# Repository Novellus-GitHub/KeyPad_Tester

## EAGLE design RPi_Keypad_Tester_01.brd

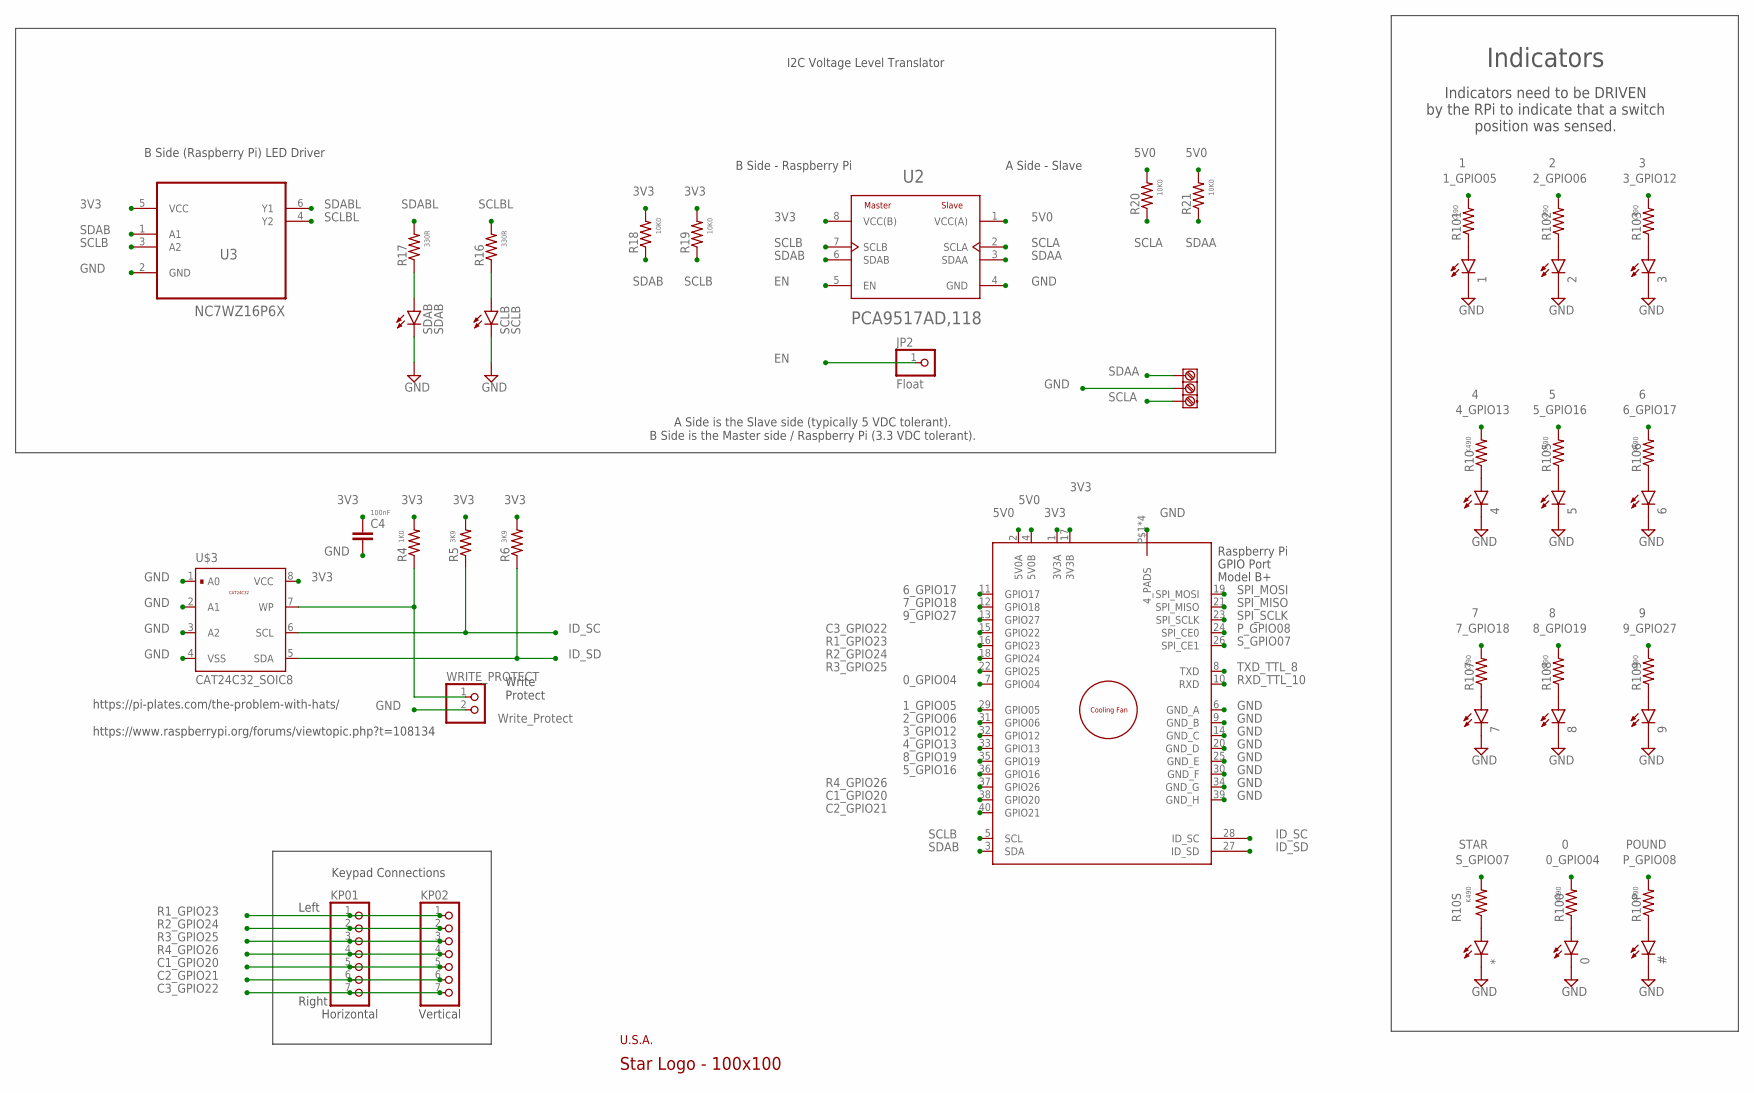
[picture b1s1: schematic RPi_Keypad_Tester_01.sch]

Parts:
0: 0; SML1206
1: 1; SML1206
2: 2; SML1206
3: 3; SML1206
4: 4; SML1206
5: 5; SML1206
6: 6; SML1206
7: 7; SML1206
8: 8; SML1206
9: 9; SML1206
#: POUND; SML1206
*: STAR; SML1206
C4: 100nF; C0805
JP2: Float; 1X01
KP01: PINHD-1X7/90; 1X07/90
KP02: PINHD-1X7; 1X07
R4: 1K0; RES_1206
R5, R6: 3K9; RES_1206
R10, R10P, R10S, R100, R101, R102, R103, R105, R106, R107, R108, R109: K490; RES_1206
R16, R17: 330R; RES_1206
R18, R19, R20, R21: 10K0; RES_1206
SCLB: SCLB; SML1206
SDAB: SDAB; SML1206
U2: PCA9517AD,118; SOIC127P600X175-8N
U3: NC7WZ16P6X; SOT65P210X110-6N
U$1: USA_01
U$2: 3_POSITION_3.81
U$3: CAT24C32_SOIC8
U$4: STAR_LOGO_01
WRITE_PROTECT: Write_Protect; 1X02
X1: RASPI_BOARD_B+#2_HDC; RASPI_BOARD_B+HAT_DF_CF

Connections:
0_GPIO04: R100.2, X1.7 (GPIO04)
1_GPIO05: R101.2, X1.29 (GPIO05)
2_GPIO06: R102.2, X1.31 (GPIO06)
3V3: C4.1, R4.2, R5.2, R6.2, R18.2, R19.2, U2.8 (VCC(B)), U3.5 (VCC), U$3.8 (VCC), X1.1 (3V3A), X1.17 (3V3B)
3_GPIO12: R103.2, X1.32 (GPIO12)
4_GPIO13: R10.2, X1.33 (GPIO13)
5V0: R20.2, R21.2, U2.1 (VCC(A)), X1.2 (5V0A), X1.4 (5V0B)
5_GPIO16: R105.2, X1.36 (GPIO16)
6_GPIO17: R106.2, X1.11 (GPIO17)
7_GPIO18: R107.2, X1.12 (GPIO18)
8_GPIO19: R108.2, X1.35 (GPIO19)
9_GPIO27: R109.2, X1.13 (GPIO27)
C1_GPIO20: KP01.5, KP02.5, X1.38 (GPIO20)
C2_GPIO21: KP01.6, KP02.6, X1.40 (GPIO21)
C3_GPIO22: KP01.7, KP02.7, X1.15 (GPIO22)
EN: JP2.1, U2.5 (EN)
GND: 0.C, 1.C, 2.C, 3.C, 4.C, 5.C, 6.C, 7.C, 8.C, 9.C, #.C, *.C, C4.2, SCLB.C, SDAB.C, U2.4 (GND), U3.2 (GND), U$2.2, U$3.1 (A0), U$3.2 (A1), U$3.3 (A2), U$3.4 (VSS), WRITE_PROTECT.2, X1.6 (GND_A), X1.9 (GND_B), X1.14 (GND_C), X1.20 (GND_D), X1.25 (GND_E), X1.30 (GND_F), X1.34 (GND_G), X1.39 (GND_H), X1.P$1 (4_PADS), X1.P$2 (4_PADS), X1.P$3 (4_PADS), X1.P$4 (4_PADS)
ID_SC: R5.1, U$3.6 (SCL), X1.28 (ID_SC)
ID_SD: R6.1, U$3.5 (SDA), X1.27 (ID_SD)
ID_WP1: R4.1, U$3.7 (WP), WRITE_PROTECT.1
unnamed: 1.A, R101.1
unnamed: 2.A, R102.1
unnamed: 3.A, R103.1
unnamed: 4.A, R10.1
unnamed: 5.A, R105.1
unnamed: 6.A, R106.1
unnamed: 7.A, R107.1
unnamed: 8.A, R108.1
unnamed: 9.A, R109.1
unnamed: *.A, R10S.1
unnamed: 0.A, R100.1
unnamed: #.A, R10P.1
unnamed: R16.1, SCLB.A
unnamed: R17.1, SDAB.A
P_GPIO08: R10P.2, X1.24 (SPI_CE0)
R1_GPIO23: KP01.1, KP02.1, X1.16 (GPIO23)
R2_GPIO24: KP01.2, KP02.2, X1.18 (GPIO24)
R3_GPIO25: KP01.3, KP02.3, X1.22 (GPIO25)
R4_GPIO26: KP01.4, KP02.4, X1.37 (GPIO26)
RXD_TTL_10: X1.10 (RXD)
SCLA: R20.1, U2.2 (SCLA), U$2.1
SCLB: R19.1, U2.7 (SCLB), U3.3 (A2), X1.5 (SCL)
SCLBL: R16.2, U3.4 (Y2)
SDAA: R21.1, U2.3 (SDAA), U$2.3
SDAB: R18.1, U2.6 (SDAB), U3.1 (A1), X1.3 (SDA)
SDABL: R17.2, U3.6 (Y1)
SPI_MISO: X1.21 (SPI_MISO)
SPI_MOSI: X1.19 (SPI_MOSI)
SPI_SCLK: X1.23 (SPI_SCLK)
S_GPIO07: R10S.2, X1.26 (SPI_CE1)
TXD_TTL_8: X1.8 (TXD)

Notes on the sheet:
Write Protect
https://pi-plates.com/the-problem-with-hats/ https://www.raspberrypi.org/forums/viewtopic.php?t=108134
Keypad Connections
Vertical
Horizontal
A Side is the Slave side (typically 5 VDC tolerant). B Side is the Master side / Raspberry Pi (3.3 VDC tolerant).
I2C Voltage Level Translator
B Side (Raspberry Pi) LED Driver
B Side - Raspberry Pi
A Side - Slave
Left
Right
Indicators
Indicators need to be DRIVEN by the RPi to indicate that a switch position was sensed.

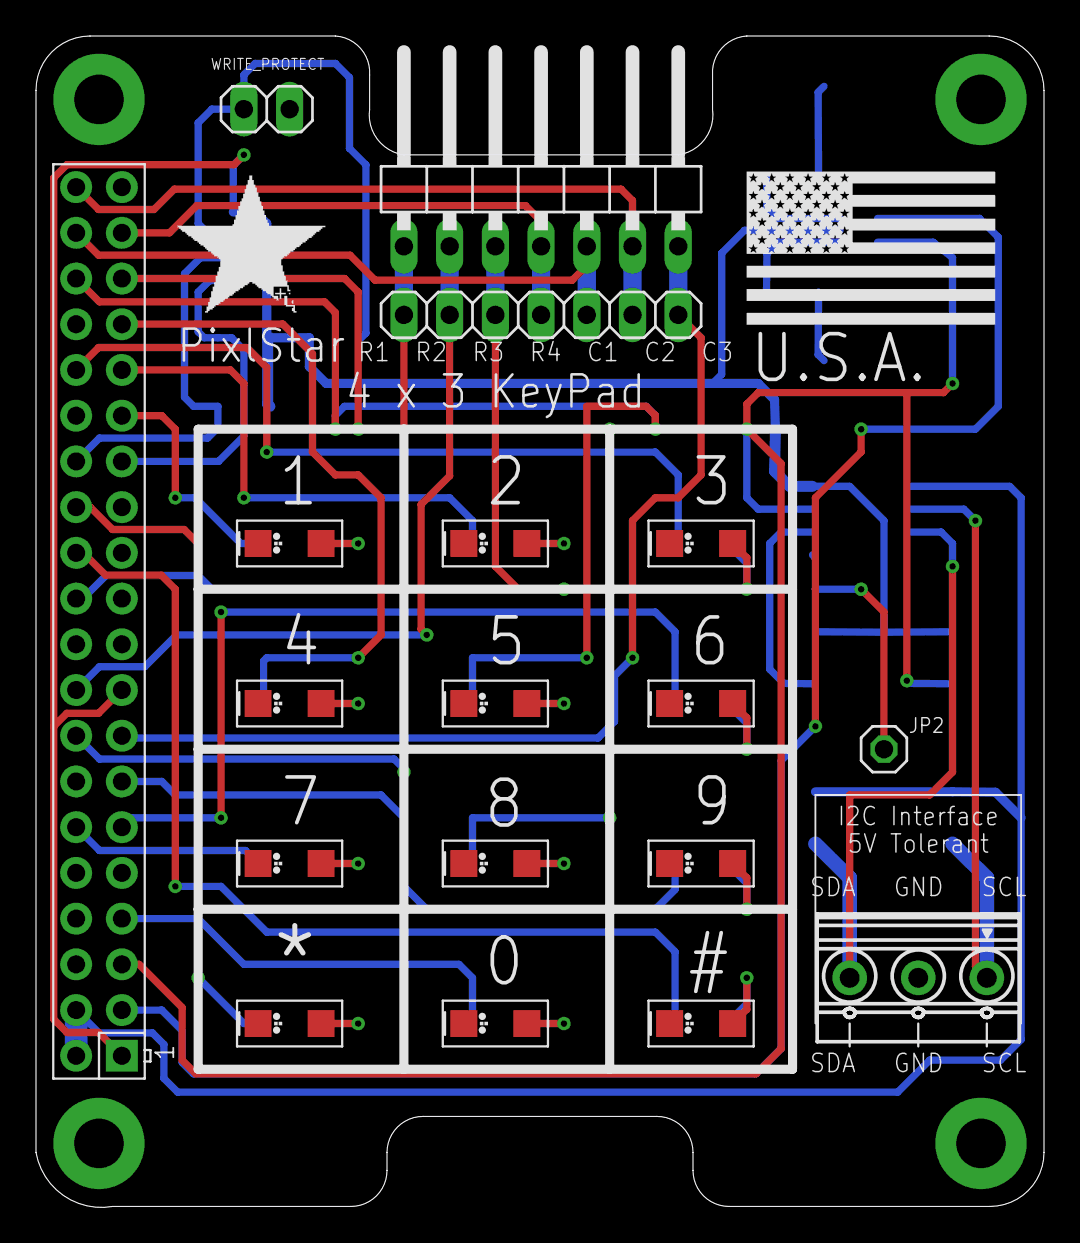
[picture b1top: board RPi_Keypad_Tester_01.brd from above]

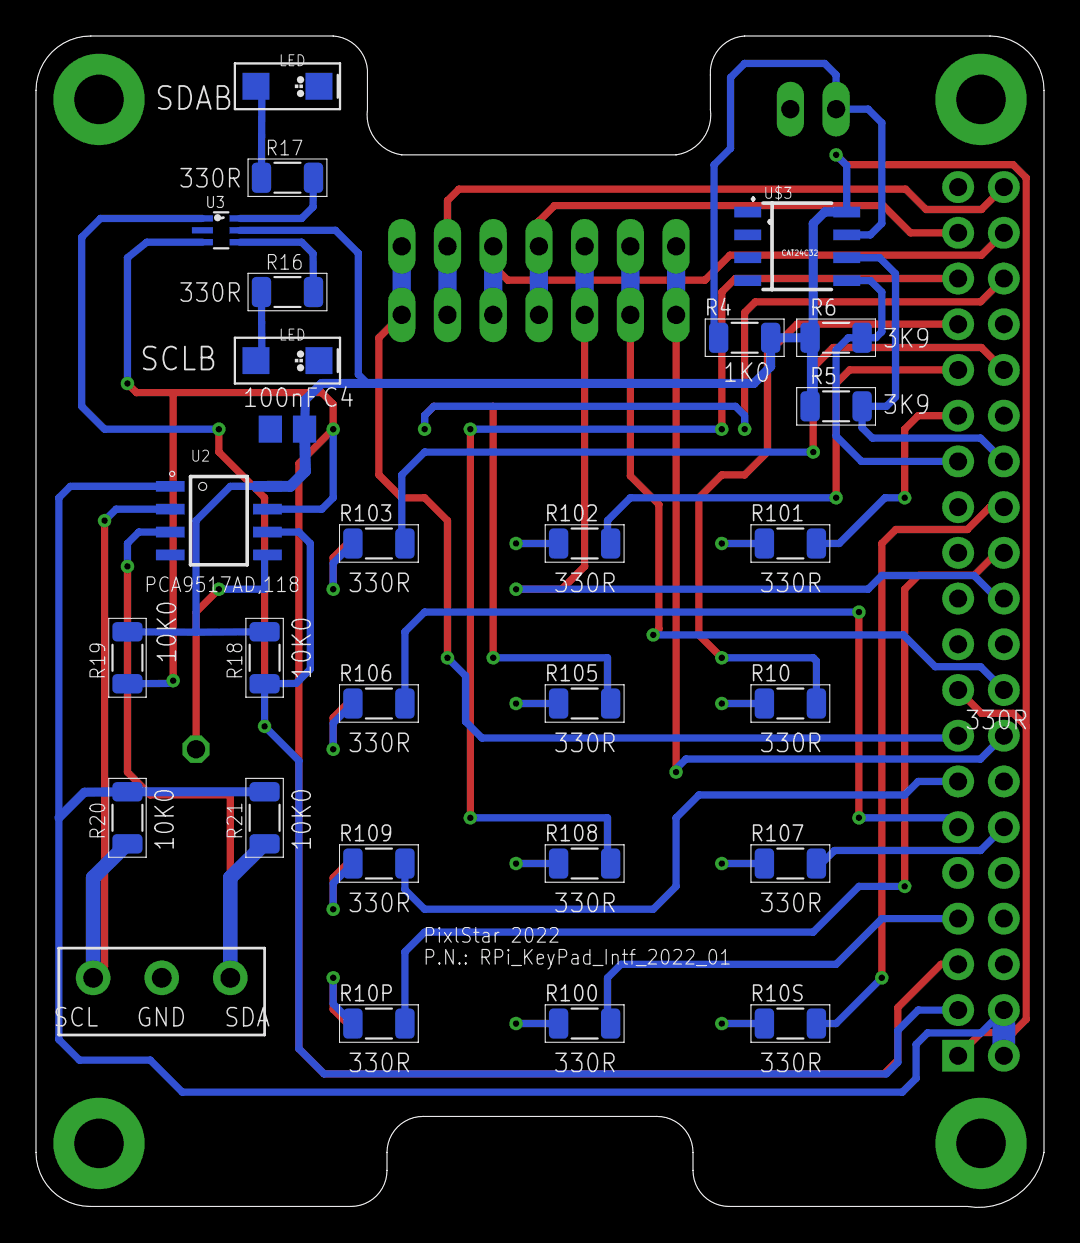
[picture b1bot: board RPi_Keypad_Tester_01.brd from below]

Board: 2 copper layers, 56.0 x 65.1 mm, 47 parts (27 on the bottom side), 46 nets.
